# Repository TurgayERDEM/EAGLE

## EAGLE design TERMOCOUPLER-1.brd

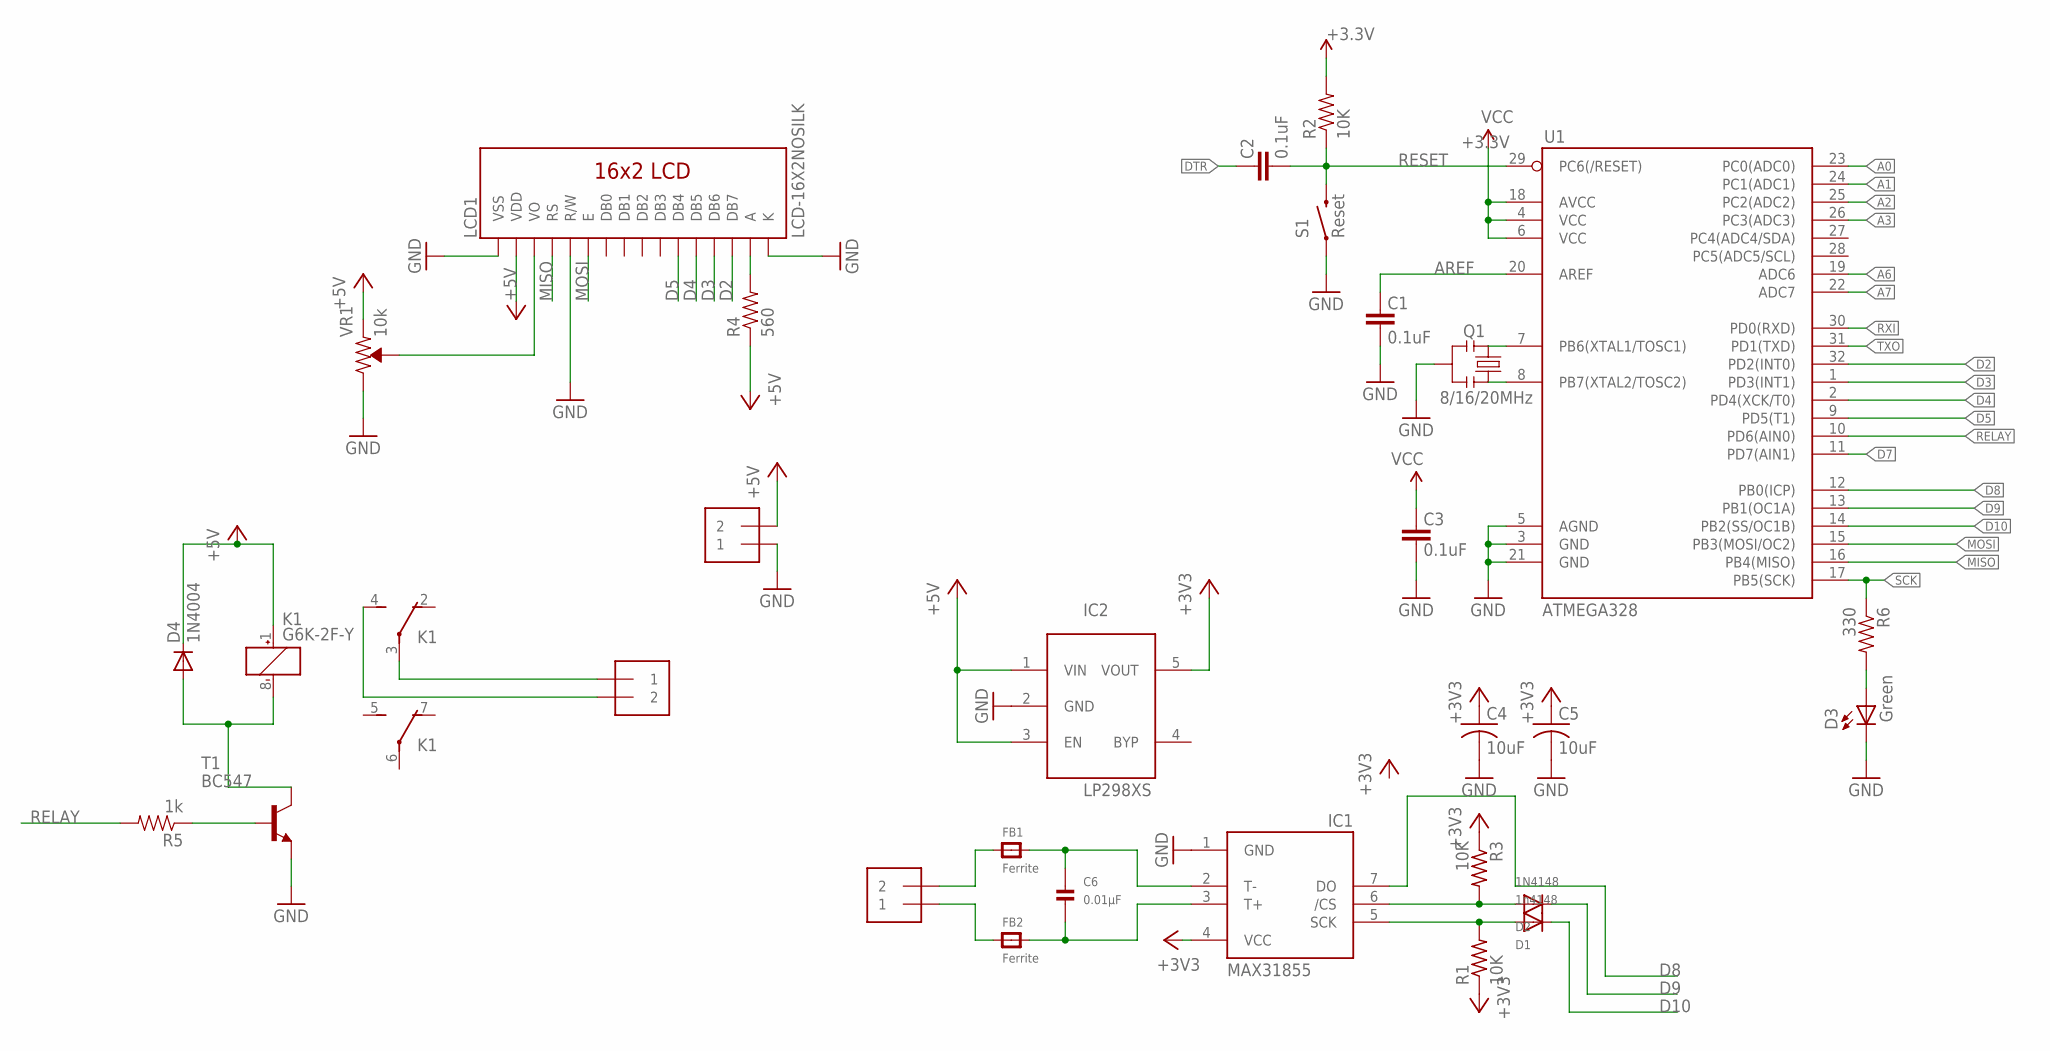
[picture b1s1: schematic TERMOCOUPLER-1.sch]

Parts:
C1, C2, C3: 0.1uF; 0603-CAP
C4, C5: 10uF; C0805K
C6: 0.01µF; _0805
D1: 1n4148; SOD-323F
D2: 1N4148; SOD-323F
D3: Green; 0603-LED-ALT1
D4: 1N4004; DO41-10
FB1, FB2: Ferrite; _0805
IC1: MAX31855; SO08
IC2: LP298XS; SOT23-5L
J1, J2, J3: 1X2-3.5MM
K1: G6K-2F-Y
LCD1: LCD-16X2NOSILK; LCD-16X2_NOSILK
Q1: 8/16/20MHz; RESONATOR-SMD-1:1
R1, R3: 10K; R0805
R2: 10K; 0603-RES
R4: 560; 0603-RES
R5: 1k; 0603-RES
R6: 330; 0603-RES
S1: Reset; TACTILE-SWITCH-SMD-ALT01
T1: BC547; TO92
U1: ATMEGA328; TQFP32-08
VR1: 10k; TRIMPOT-SMD-3MM-CLOSED

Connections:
+3.3V: C3.2, R2.2, U1.4 (VCC), U1.6 (VCC), U1.18 (AVCC)
+3V3: C4.1, C5.1, IC1.4 (VCC), IC2.5 (VOUT), R1.1, R3.1
+5V: D4.C, IC2.1 (VIN), IC2.3 (EN), J2.2, K1.1 (+), LCD1.2 (VDD), R4.1, VR1.1 (CCW)
A0: U1.23 (PC0(ADC0))
A1: U1.24 (PC1(ADC1))
A2: U1.25 (PC2(ADC2))
A3: U1.26 (PC3(ADC3))
A6: U1.19 (ADC6)
A7: U1.22 (ADC7)
AREF: C1.2, U1.20 (AREF)
CS: D2.A, IC1.6 (/CS), R3.2
D2: LCD1.14 (DB7), U1.32 (PD2(INT0))
D3: LCD1.13 (DB6), U1.1 (PD3(INT1))
D4: LCD1.12 (DB5), U1.2 (PD4(XCK/T0))
D5: LCD1.11 (DB4), U1.9 (PD5(T1))
D7: U1.11 (PD7(AIN1))
D8: IC1.7 (DO), U1.12 (PB0(ICP))
D9: D2.C, U1.13 (PB1(OC1A))
D10: D1.C, U1.14 (PB2(SS/OC1B))
DTR: C2.2
GND: C1.1, C3.1, C4.2, C5.2, D3.C, IC1.1 (GND), IC2.2 (GND), J2.1, LCD1.1 (VSS), LCD1.5 (R/W), LCD1.16 (K), Q1.2, S1.1, S1.2 (1), T1.1 (E), U1.3 (GND), U1.5 (AGND), U1.21 (GND), VR1.3 (CW)
MISO: LCD1.4 (RS), U1.16 (PB4(MISO))
MOSI: LCD1.6 (E), U1.15 (PB3(MOSI/OC2))
unnamed: Q1.3, U1.8 (PB7(XTAL2/TOSC2))
unnamed: Q1.1, U1.7 (PB6(XTAL1/TOSC1))
unnamed: J3.1, K1.3
unnamed: D4.A, K1.8 (-), T1.3 (C)
unnamed: FB1.1, J1.2
unnamed: C6.1, FB1.2, IC1.2 (T-)
unnamed: D3.A, R6.2
unnamed: FB2.1, J1.1
unnamed: C6.2, FB2.2, IC1.3 (T+)
unnamed: J3.2, K1.4 (S)
unnamed: R5.1, T1.2 (B)
unnamed: LCD1.15 (A), R4.2
unnamed: LCD1.3 (VO), VR1.2 (WIPER)
RELAY: R5.2, U1.10 (PD6(AIN0))
RESET: C2.1, R2.1, S1.3 (2), S1.4 (2), U1.29 (PC6(/RESET))
RXI: U1.30 (PD0(RXD))
SCK: R6.1, U1.17 (PB5(SCK))
SCK1: D1.A, IC1.5 (SCK), R1.2
TXO: U1.31 (PD1(TXD))

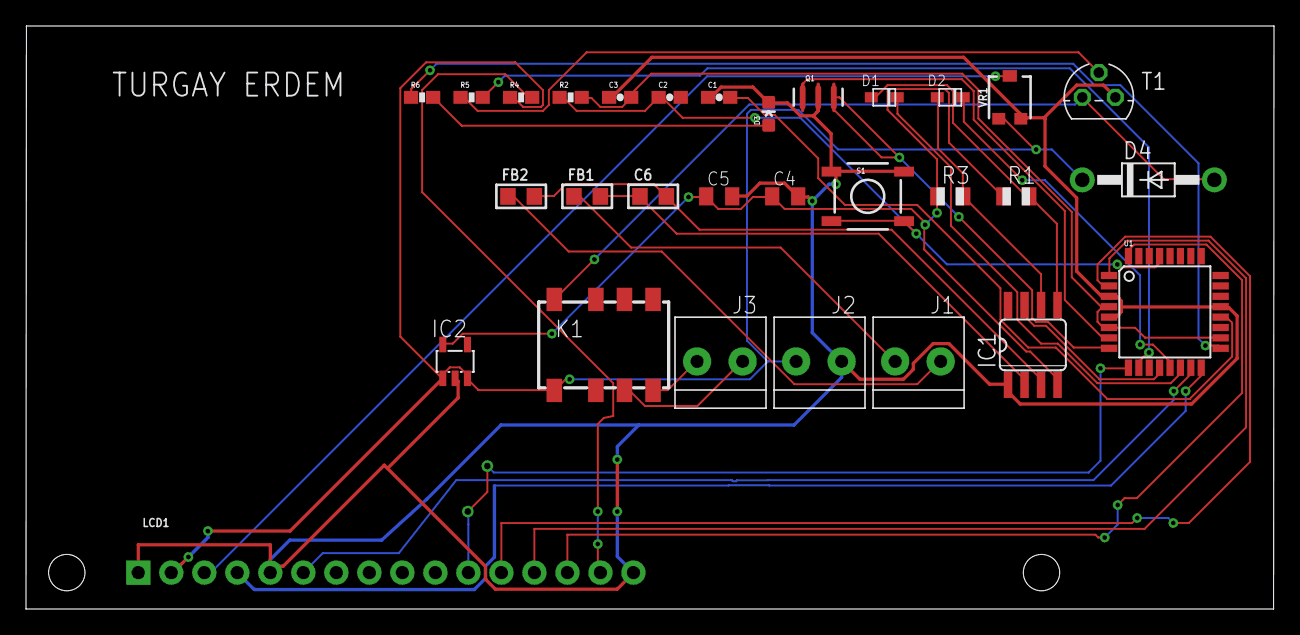
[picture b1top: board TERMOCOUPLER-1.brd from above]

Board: 2 copper layers, 96.0 x 44.9 mm, 30 parts (0 on the bottom side), 32 nets.

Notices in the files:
parts and their libraries:
SparkFun-Displays: Licensing: Creative Commons ShareAlike 4.0 International - https://creativecommons.org/licenses/by-sa/4.0
